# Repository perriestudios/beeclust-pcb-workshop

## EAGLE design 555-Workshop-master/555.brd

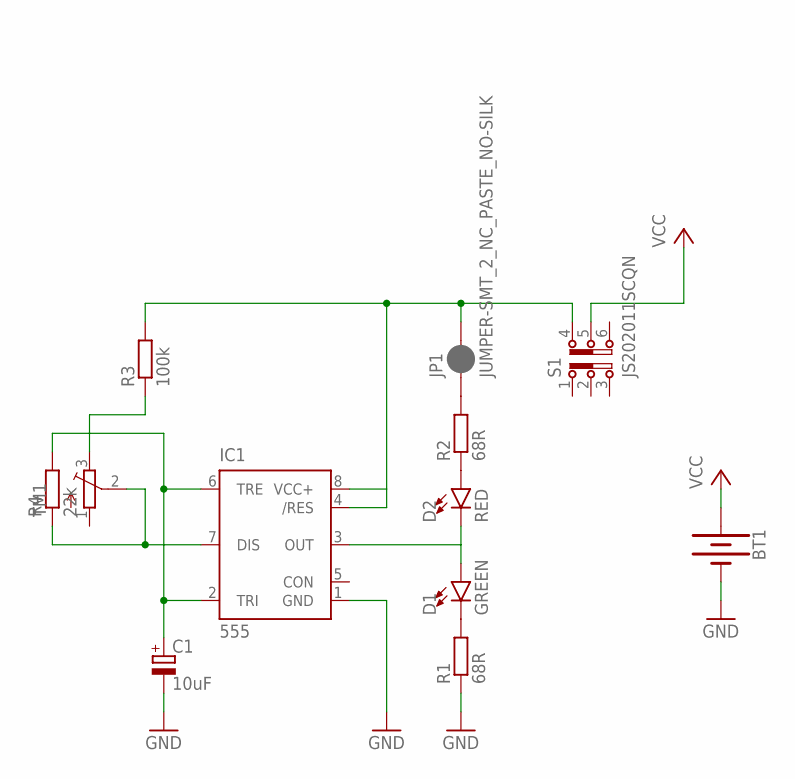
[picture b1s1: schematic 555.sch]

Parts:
BT1: BATTERY-20MM_SMD; BATTCON_20MM
C1: 10uF; SMC_A
D1: GREEN; LED-1206
D2: RED; LED-1206
IC1: 555; SO08
JP1: JUMPER-SMT_2_NC_PASTE_NO-SILK; SMT-JUMPER_2_NC_PASTE_NO-SILK
R1, R2: 68R; R0603
R3: 100k; R0603
R4: 22k; R0603
S1: JS202011SCQN
TM1: TRIMPOTTC33X; TC33X

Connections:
GND: BT1.2 (-), C1.-, IC1.1 (GND), R1.1
unnamed: C1.+, IC1.2 (TRI), IC1.6 (TRE), R4.2
unnamed: IC1.4 (/RES), IC1.8 (VCC+), JP1.2, R3.2, S1.4
unnamed: IC1.7 (DIS), R4.1, TM1.2 (S)
unnamed: D1.C, R1.2
unnamed: D1.A, D2.C, IC1.3 (OUT)
unnamed: D2.A, R2.1
unnamed: JP1.1, R2.2
unnamed: R3.1, TM1.3 (E)
VCC: BT1.1 (+), S1.5

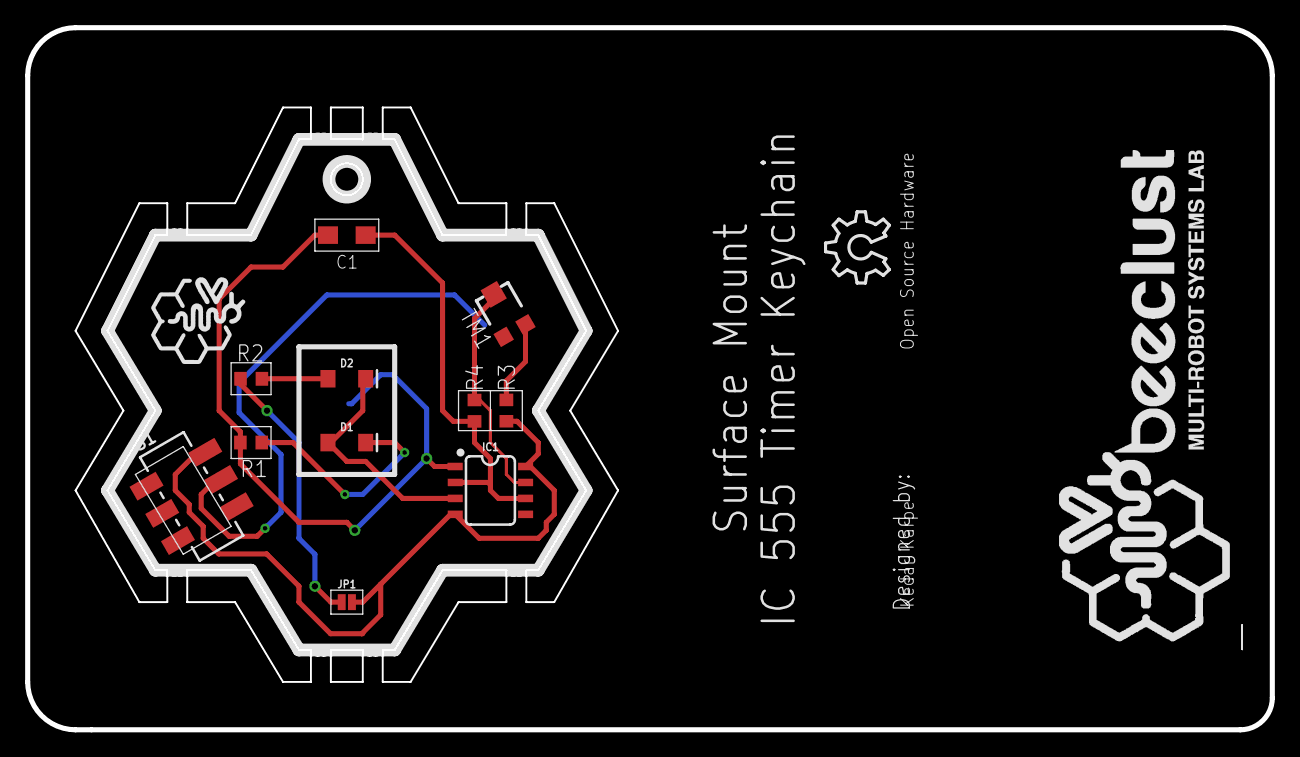
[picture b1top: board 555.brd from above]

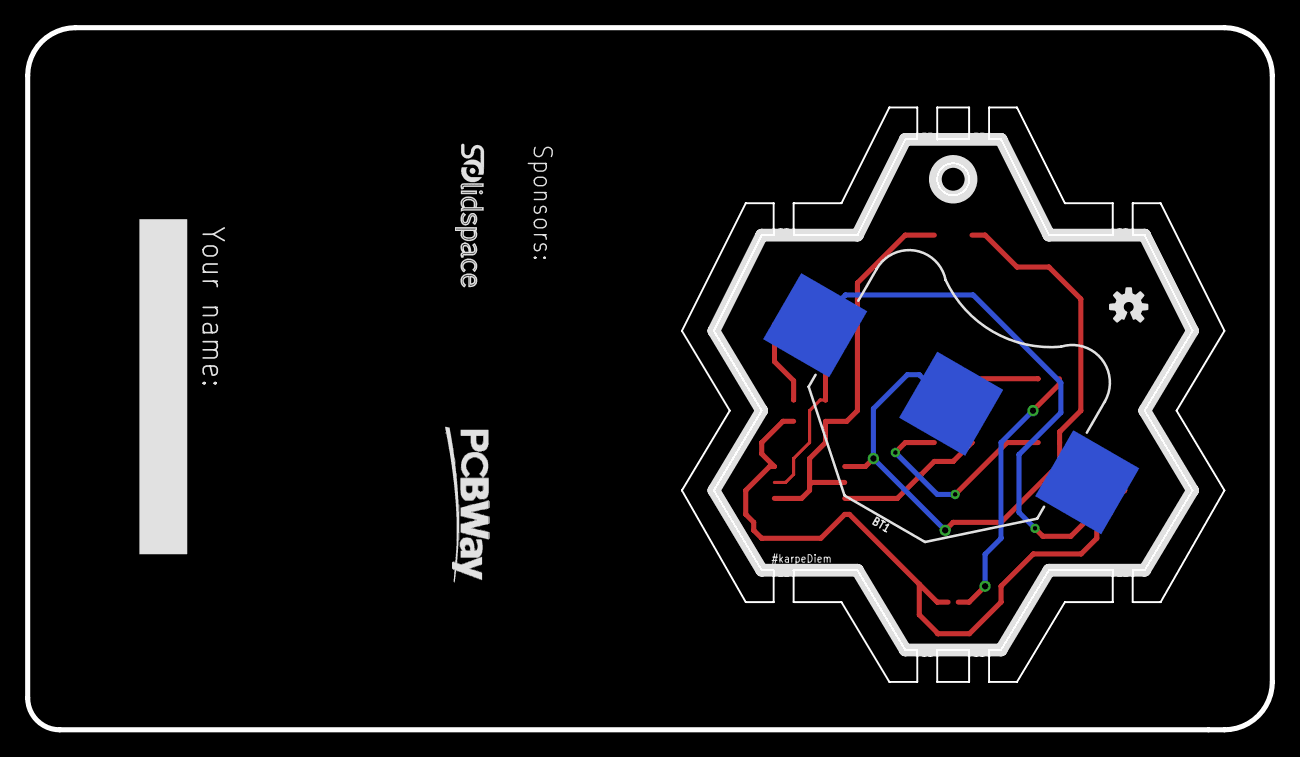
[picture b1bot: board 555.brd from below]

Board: 2 copper layers, 99.1 x 55.9 mm, 18 parts (4 on the bottom side), 10 nets.

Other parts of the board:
U$2: LOGO-L
U$3: OSHW_10X200_NOTEXT
U$4: LOGO-NONAME
U$5: OSHW-LOGO-S
U$6: PCBWAYLOGO-M
U$7: SOLIDSPACELOGO-M

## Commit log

2020-11-17 Added the files

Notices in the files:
parts and their libraries:
SparkFun-IC-Special-Function: Licensing: Creative Commons ShareAlike 4.0 International - https://creativecommons.org/licenses/by-sa/4.0
slide: Copyright (C) 2011, Bob Starr
